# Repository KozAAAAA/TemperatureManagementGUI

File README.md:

# Temperature Manangement GUI

<p align="center">
  The Raspberry Pi GUI that lets you control the temperature of a chamber.
</p>

## Key feautures
* The **temperature** values are settable (GUI).
* The **time** periods are settable (GUI).
* The number of **repeats** is settable (GUI).
* The **hysteresis** value is customizable (settings.h).
* **Relay** & **Fan** RPi **pins** are customizable (settings.h).
* Compiles on **arm** as well as **x86** thanks to the use of **preprocessor** & **qmake**.
* Puts controlled **GPIO** pins to **LOW** if program is turned off.
* Displays **error messages** whenever **python script** or **txt file** is unavailable.
* Checks whether the read **temperature** is valid.
* Hardware uses **PT100** & **custom PCB** to read the temperature via the **SPI protocol**.
* Temperature is **controlled** via the **relay**.
* All of the important data displays if the start button is clicked.
* made with **C++17**, **QML** & **Python**
## User Flow Diagram

## Hardware
The circuit shown below is the Raspberry Pi hat that makes **temperature reading** & **relay control** possible.

## Installation

Raspbian installation:

```bash
  coming soon...
```

## License

All code is released under the [MIT](https://choosealicense.com/licenses/mit/) License.

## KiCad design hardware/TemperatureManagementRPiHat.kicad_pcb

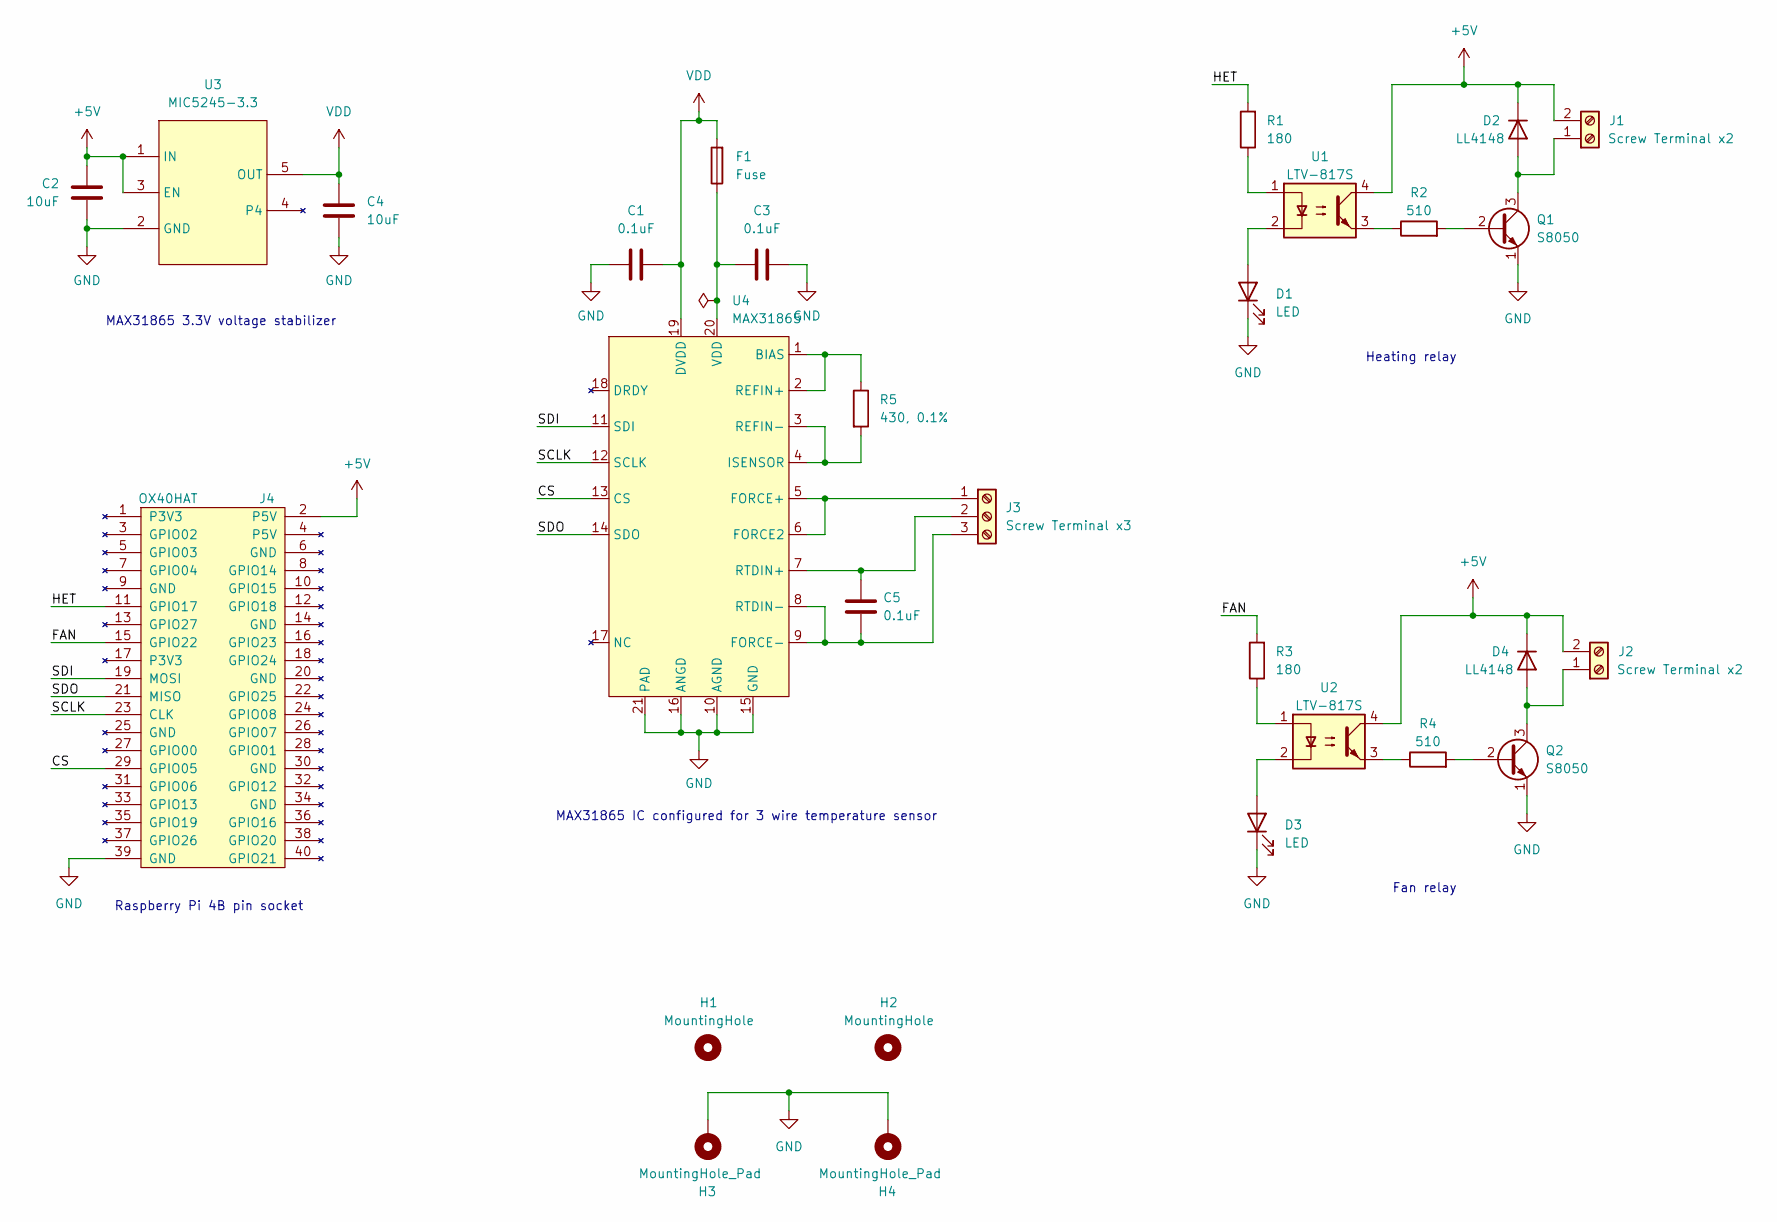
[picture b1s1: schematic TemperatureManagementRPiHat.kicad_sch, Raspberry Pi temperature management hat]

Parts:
C1, C3, C5: 0.1uF; C_0603_1608Metric_Pad1.08x0.95mm_HandSolder
C2, C4: 10uF; C_0603_1608Metric_Pad1.08x0.95mm_HandSolder
D1, D3: LED; LED_0603_1608Metric_Pad1.05x0.95mm_HandSolder
D2, D4: LL4148; D_MiniMELF
F1: Fuse; Fuse_0603_1608Metric_Pad1.05x0.95mm_HandSolder
H1, H2: MountingHole; MountingHole_3mm
H3, H4: MountingHole_Pad; MountingHole_3mm_Pad
J1, J2: Screw Terminal x2; TerminalBlock_Phoenix_PT-1,5-2-3.5-H_1x02_P3.50mm_Horizontal
J3: Screw Terminal x3; TerminalBlock_Phoenix_PT-1,5-3-3.5-H_1x03_P3.50mm_Horizontal
J4: OX40HAT; PinSocket_2x20_P2.54mm_Vertical
Q1, Q2: S8050; SOT-23_Handsoldering
R1, R3: 180; R_0603_1608Metric_Pad0.98x0.95mm_HandSolder
R2, R4: 510; R_0603_1608Metric_Pad0.98x0.95mm_HandSolder
R5: 430, 0.1%; R_0603_1608Metric_Pad0.98x0.95mm_HandSolder
U1, U2: LTV-817S; SMDIP-4_W9.53mm
U3: MIC5245-3.3; SOT-23-5_HandSoldering
U4: MAX31865; TQFN-20-1EP_5x5mm_P0.65mm_EP3.1x3.1mm

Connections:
+5V: C2.2, D2.1 (K), D4.1 (K), J1.2, J2.2, J4.2 (P5V), U1.4, U2.4, U3.1 (IN), U3.3 (EN)
/CS: J4.29 (GPIO05), U4.13 (CS)
/FAN: J4.15 (GPIO22), R3.2
/HET: J4.11 (GPIO17), R1.2
/SCLK: J4.23 (CLK), U4.12 (SCLK)
/SDI: J4.19 (MOSI), U4.11 (SDI)
/SDO: J4.21 (MISO), U4.14 (SDO)
GND: C1.2, C2.1, C3.1, C4.2, D1.1 (K), D3.1 (K), H3.1, H4.1, J4.39 (GND), Q1.1 (E), Q2.1 (E), U3.2 (GND), U4.10 (AGND), U4.15 (GND), U4.16 (ANGD), U4.21 (PAD)
unnamed: C3.2, F1.1, U4.20 (VDD)
unnamed: C5.1, J3.2, U4.7 (RTDIN+)
unnamed: C5.2, J3.3, U4.8 (RTDIN-), U4.9 (FORCE-)
unnamed: D1.2 (A), U1.2
unnamed: D2.2 (A), J1.1, Q1.3 (C)
unnamed: D3.2 (A), U2.2
unnamed: D4.2 (A), J2.1, Q2.3 (C)
unnamed: Q1.2 (B), R2.2
unnamed: Q2.2 (B), R4.2
unnamed: R1.1, U1.1
unnamed: R2.1, U1.3
unnamed: R3.1, U2.1
unnamed: R4.1, U2.3
unnamed: R5.1, U4.1 (BIAS), U4.2 (REFIN+)
unnamed: R5.2, U4.3 (REFIN-), U4.4 (ISENSOR)
unnamed: J3.1, U4.5 (FORCE+), U4.6 (FORCE2)
VDD: C1.1, C4.1, F1.2, U3.5 (OUT), U4.19 (DVDD)

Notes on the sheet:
MAX31865 3.3V voltage stabilizer
Raspberry Pi 4B pin socket
Heating relay
Fan relay
MAX31865 IC configured for 3 wire temperature sensor

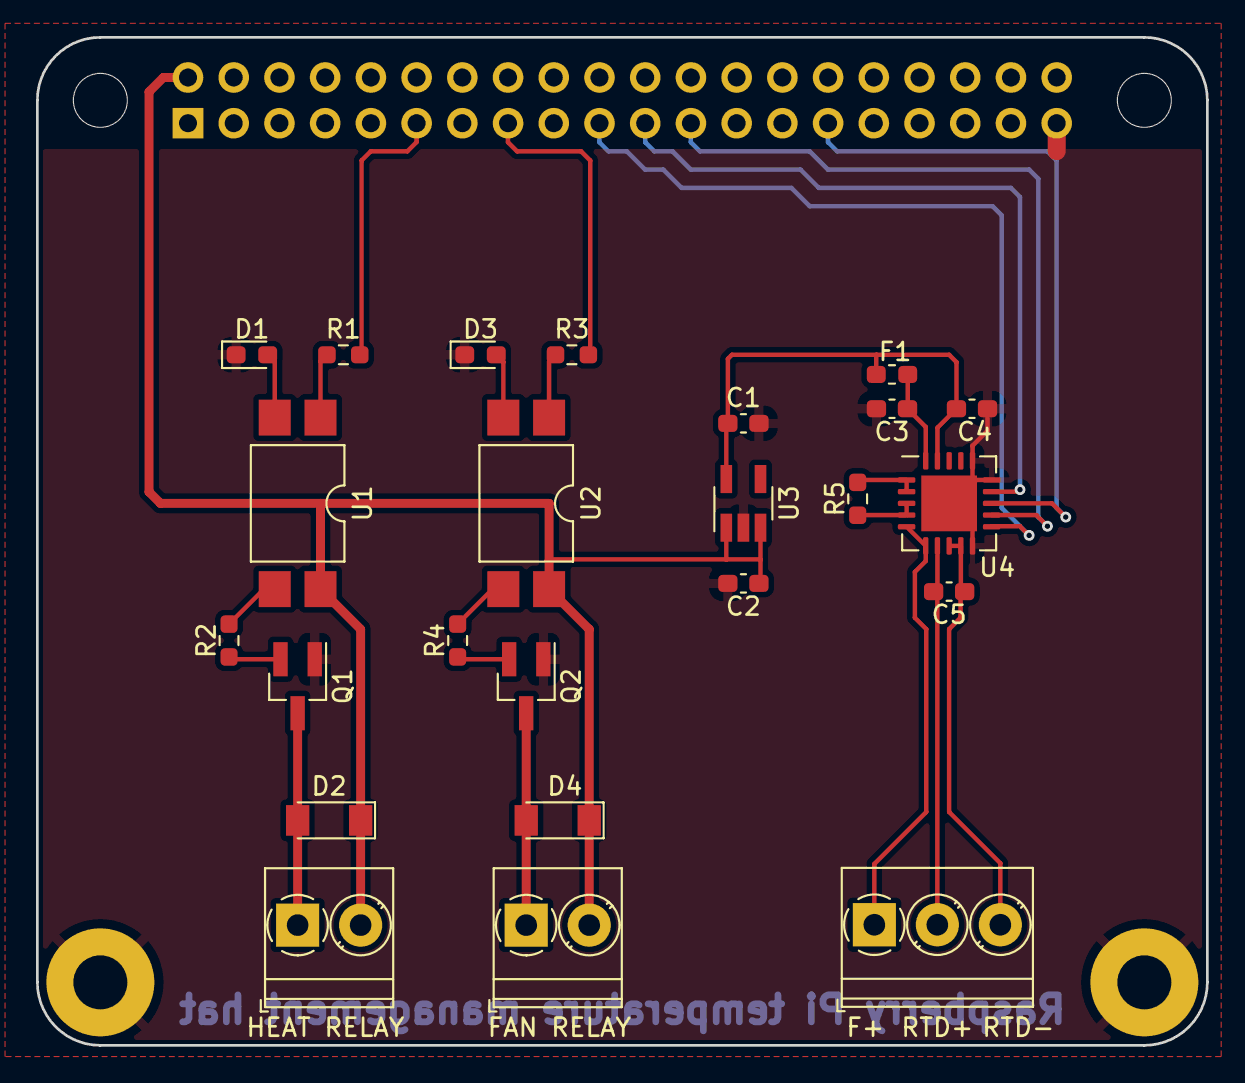
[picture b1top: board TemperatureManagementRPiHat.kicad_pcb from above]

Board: 2 copper layers, 65.0 x 56.0 mm, 29 parts (1 on the bottom side), 25 nets.

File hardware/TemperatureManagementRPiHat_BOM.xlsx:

Item | Name | Qty | Reference | Price | Part page
1 | Capacitor 0.1uF | 3 | C1, C3, C5 | 1.326 | https://www.mouser.pl/ProductDetail/Samsung-Electro-Mechanic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
2 | Capacitor 10uF | 2 | C2, C4 | 1.684 | https://www.mouser.pl/ProductDetail/Samsung-Electro-Mechanic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
3 | Red LED | 2 | D1, D3 | 2.3 | https://www.mouser.pl/ProductDetail/Lite-On/LTST-C191KRKT?qs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
4 | Diode LL4148 | 2 | D2, D4 | 1.154 | https://www.mouser.pl/ProductDetail/onsemi-Fairchild/LL4148?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
5 | Fuse 50mA | 1 | F1 | 3.53 | https://www.mouser.pl/ProductDetail/Kyocera-AVX/F0603G0R05FN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
6 | Screw Terminal x2 2.54mm | 2 | J1 J2 | 4.86 | https://www.mouser.pl/ProductDetail/Phoenix-Contact/1984617?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
7 | Screw Terminal x3 2.54mm | 1 | J3 | 3.53 | https://www.mouser.pl/ProductDetail/Phoenix-Contact/1984620?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
8 | Pin Socket 2x20 2.54mm | 1 | J4 | 8.46 | https://www.mouser.pl/ProductDetail/Wurth-Elektronik/6130402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
9 | Transistor NPN S8050 | 2 | Q1, Q2 | 1.86 | https://www.mouser.pl/ProductDetail/Micro-Commercial-Compone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
10 | Resistor 180Ω | 2 | R1, R3 | 0.88 | https://www.mouser.pl/ProductDetail/Panasonic/ERJ-3GEYJ181V?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
11 | Resistor 510Ω | 2 | R2, R4 | 0.88 | https://www.mouser.pl/ProductDetail/Panasonic/ERJ-3GEYJ511V?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
12 | Resistor 430Ω, 0.1% | 1 | R5 | 1.55 | https://www.mouser.pl/ProductDetail/Panasonic/ERA-3AEB431V?q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
13 | Optocoupler FOD817 | 2 | U1, U2 | 5.12 | https://www.mouser.pl/ProductDetail/onsemi-Fairchild/FOD817B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
14 | Voltage regulator MIC5245-3.3 | 1 | U3 | 3.05 | https://www.mouser.pl/ProductDetail/Microchip-Technology/MIC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
15 | IC MAX31865 | 1 | U4 | 33.15 | https://www.mouser.pl/ProductDetail/Maxim-Integrated/MAX3186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
 |  | Suma: |  | 73.334
 |  | Suma bez U1/2/4 |  | 35.064

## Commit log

2022-03-09 added the red rectangle
2022-03-15 qml -> c++ -> qml text communication v1
2022-03-15 qml -> c++ -> qml works properly, added the textbox into the Loop.qml file
2022-03-15 Changed the Loop.qml to TextBox.qml and added some new features to it.
2022-03-16 Created the GridSetupBlock, with the ability to input only 3 digit numbers
2022-03-16 Blocked the possibility of inputing anything else than numbers from the range of 0 to 200
2022-03-22 Added the LoopBlock, OutputBox, ShowBlock and changed the name from TextBox to InputBox
2022-03-23 The functioning frontend for the communication with the c++ backend
2022-03-30 Upgraded the temperaturemenagment.cpp
2022-03-30 Completed a Qml to Cpp communication. Added a method to print the variables.
2022-04-05 Completed the c++ to qml communication
2022-04-26 Completed the getTempSensor() method and declared three others to control the GPIO
2022-04-27 Added the conditional methods and includes for the ARM specific only. Deleted all the unnecesary files. Altered the behaviour of START button.
2022-05-06 Threads are workinggit add .!
2022-05-10 Competed the START-STOP functionallity - clicking the STOP button kills the qThread along with the Worker
2022-05-10 Sending to and reciving data from the second thread works. There is a need to change all of the ints to qints
2022-05-12 Changed the uint_t types to quint
2022-05-12 Added cathegories to the worker class and edited the run() method. Elapsed time has to be added
2022-05-17 Time, loop and block changing works. Time is displayed in hh::mm::ss format. Button changes to START when WORKER is deleted. Program won't start if the variable loopInput is equal to 0.
2022-05-20 Heating indication has been added. Program wont start when neither of timers is on.
2022-05-24 Ugly GUI - fully functional - time for something good-looking
2022-05-25 A working RaspberryPi version
2022-05-30 Font file and Fontloader have been added
2022-05-31 SetupBlock2 has been added, along with the IntputBox2 and ToggleSwitch2
2022-06-02 Added the LoopSpinBox2
2022-06-02 StartButton2 has been added - not functional yet
2022-06-04 GridSetupBlocks2 works
2022-06-04 GUI 2.0 - ain't no animations yet
2022-06-04 Readme edit
2022-06-07 'set to' works
2022-06-07 Animations have been added
2022-06-07 'set to' has been polished - no more 'unknown'
2022-06-07 The animation of the LoopSpinBox2 has been added
2022-06-08 gif has changed
2022-06-08 StartButton2 color shifts nad scale animations.
2022-06-14 Push before vector to queue change
2022-06-14 Time spinbox has been changed to floating point
2022-06-14 ShowHeating indicator animation
2022-06-14 throw, try, catch, for the unopenable .py and .txt have been added.
2022-06-14 A more readible files structure
2022-06-15 software and hardware distinction
2022-06-19 Error property has been added. Worker to MainGui error passing has to be added.
2022-06-20 Exception messege thrown by the Worker is now received in the MainGui
2022-06-20 Exception message is displayed in qml
2022-06-20 A centered Dialog
2022-06-20 script paths have been changed
2022-06-21 Input Parameters Printing has been optimised.
2022-06-25 c style array -> std::array
2022-06-29 std::vector -> std::array
2022-06-29 setFanOn() and setFanOff() have been added
2022-06-29 kicad .gitignore
2022-06-29 push before krzychu
2022-06-29 hardware push - krzychu
2022-06-29 A working arm & x86 version
2022-07-04 Precompiled headers
2022-07-04 Time imput box has been repaired
2022-07-04 Changing the state of the setup is now prohibited
2022-07-04 Bad temperature reading handling has been implemented
2022-07-04 PCB board V2
2022-07-05 final version of V2 board with gerber files
2022-07-05 stencil gerber file added
2022-07-05 App shutdown is now handled by the std::atexit() function, wiringPi setup has been moved to main.cpp, catch for every exception has been added.
2022-07-06 Automated executable directory finder v1.0 - optimization is needed
2022-07-07 some unimportant changes
2022-07-07 Readme
2022-07-09 python files have been formatted
2022-07-11 Exceptions are safer (no GUI action, just termination), garbage readTemp value fixed
2022-07-11 #2 Bug fix - impossible to spawn more than one worker
2022-07-11 Start/Stop button is unclickable until the transition ends
2022-07-11 else if in hysteresis has been added
2022-07-13 Error messages without the use of try and catch (safer, as QT states so)
2022-07-13 Cleaner code, removed the resetOutput method, removed the unnecessary code
2022-07-13 MainGui - warnings repairs
2022-07-13 Worker - warnings repairs
2022-07-15 Worker (run & hysteresis) has been optimised
2022-07-15 added renders to readme
2022-07-15 cropped render image
